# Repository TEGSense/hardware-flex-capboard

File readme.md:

# TEG Sense Flex Capacitor Board

This is a capacitor board designed to minimize the footprint of the capacitors used for the TEGSense device.
It is meant to be paired with the [flex hardware](https://github.com/TEGSense/hardware-flex-capboard).

## License

Shield: [![CC BY-SA 4.0][cc-by-sa-shield]][cc-by-sa]

This work is licensed under a
[Creative Commons Attribution-ShareAlike 4.0 International License][cc-by-sa].

[![CC BY-SA 4.0][cc-by-sa-image]][cc-by-sa]

[cc-by-sa]: http://creativecommons.org/licenses/by-sa/4.0/
[cc-by-sa-image]: https://licensebuttons.net/l/by-sa/4.0/88x31.png
[cc-by-sa-shield]: https://img.shields.io/badge/License-CC%20BY--SA%204.0-lightgrey.svg

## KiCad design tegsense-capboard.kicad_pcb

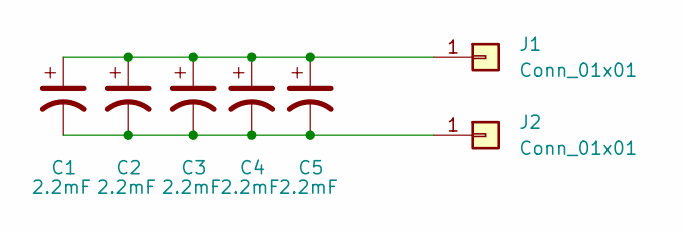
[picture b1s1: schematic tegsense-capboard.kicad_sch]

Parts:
C1, C2, C3, C4, C5: 2.2mF; C_2824_7260-20
J1, J2: Conn_01x01; Pin_D1.3mm_L11.0mm_LooseFit

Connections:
unnamed: C1.1, C2.1, C3.1, C4.1, C5.1, J1.1
unnamed: C1.2, C2.2, C3.2, C4.2, C5.2, J2.1

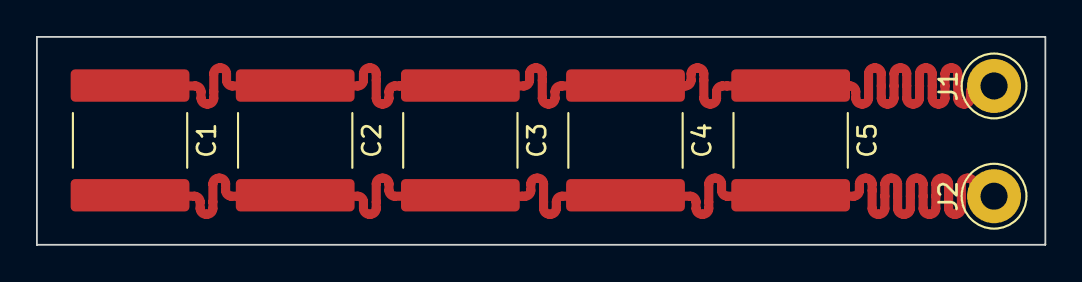
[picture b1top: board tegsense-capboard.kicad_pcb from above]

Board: 2 copper layers, 56.0 x 11.5 mm, 7 parts (0 on the bottom side), 2 nets.

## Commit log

2024-06-28 Initial.
2024-06-28 Updated KiCAD version and added image.
